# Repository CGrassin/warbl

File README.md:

# WARBL

Fork of the WARBL MIDI wind controller by Andrew Mowry (https://warbl.xyz/).

Adapted layout for 2 layers PCB and USB-C connector - Charles Grassin & [Raphaël Casimir](https://github.com/raphaelcasimir)

## Fabrication notes
You will have to cut the pins of the jack connector so they do not short with the USB-C supports.

## License

WARBL is Open Hardware and is licensed under the CERN OHL version 1.2 and the GNU General Public License.

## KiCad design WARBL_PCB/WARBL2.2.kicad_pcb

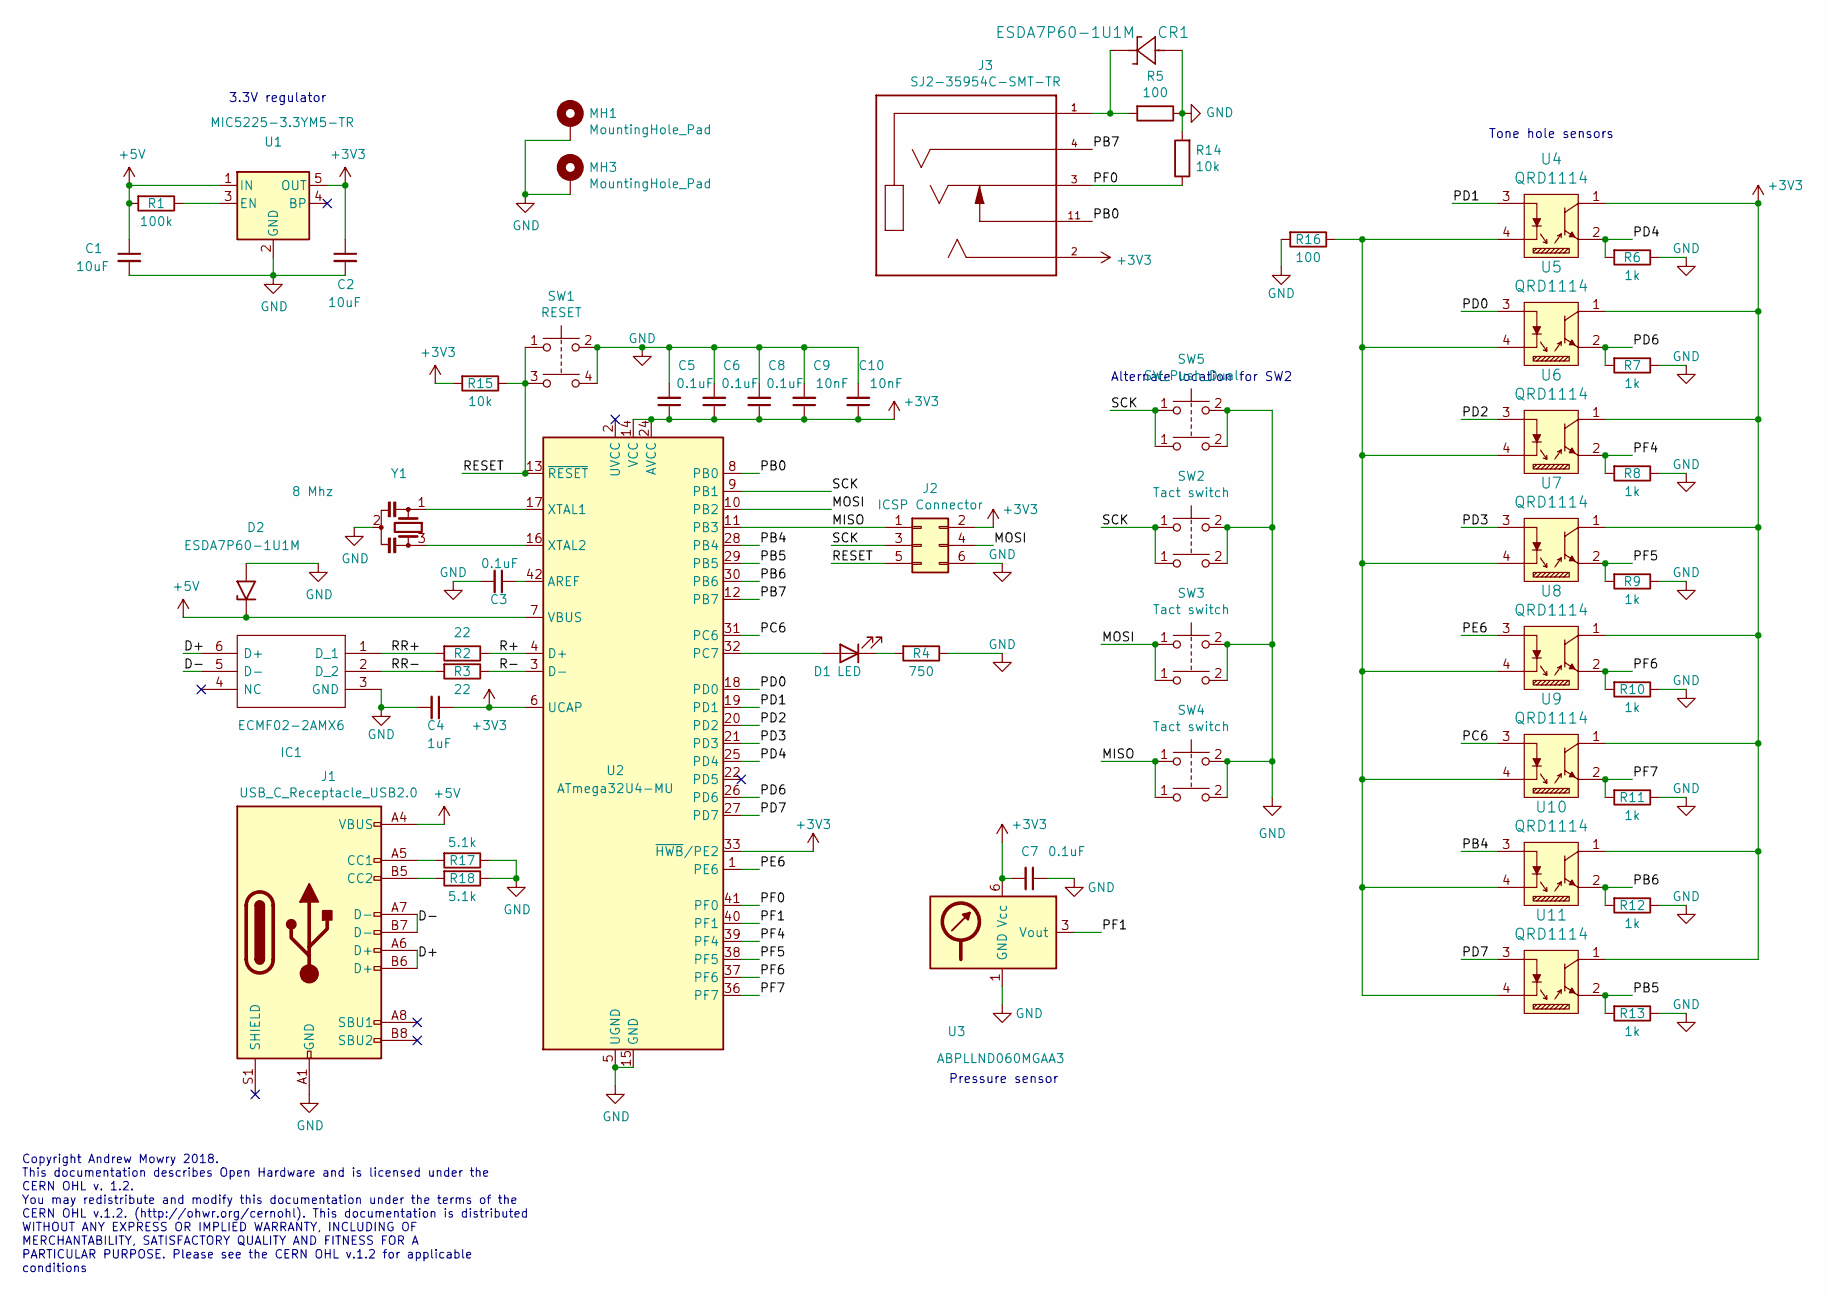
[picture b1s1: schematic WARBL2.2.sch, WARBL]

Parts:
C1, C2: 10uF; C_0603; Mfg Part # CL10A106KQ8NNNC
C3, C5, C6, C7, C8: 0.1uF; C_0603; Mfg Part # CL10F104ZB8NNNC; Digi-Key_PN 0.1µF -20%, +80% 50V Ceramic Capacitor 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
C4: 1uF; C_0603; Mfg Part # CL10B105KP8NNNC
C9, C10: 10nF; C_0603; Mfg Part # CL10B103KB8NCNC; Digi-Key_PN 10000pF ±10% 50V Ceramic Capacitor X7R 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
CR1: ESDA7P60-1U1M
D1: LED; LED_0603; Mfg Part # LG L29K-G2J1-24-Z
D2: ESDA7P60-1U1M; D_DO-201AE_P15.24mm_Horizontal; Mfg Part # ESDA7P60-1U1M
IC1: ECMF02-2AMX6; SON50P150X170X55-6N-D; Mfg Part # ECMF02-2AMX6
J1: USB_C_Receptacle_USB2.0; USB_C_Receptacle_HRO_TYPE-C-31-M-12
J2: ICSP Connector; PinHeader_2x03_P2.54mm_Vertical
J3: SJ2-35954C-SMT-TR; WARBL_CUI_SJ2-35954C-SMT-TR
MH1, MH3: MountingHole_Pad; MountingHole_0.089in_2_56_Pad
R1: 100k; R_0603; Mfg Part # ERJ-3EKF1003V; Digi-Key_PN 100 kOhms ±1% 0.1W, 1/10W Chip Resistor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
R2, R3: 22; R_0603_1608Metric; Mfg Part # ERJ-3EKF22R0V; Digi-Key_PN 22 Ohms ±1% 0.1W, 1/10W Chip Resistor 0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
R4: 750; R_0603; Mfg Part # ERJ-3GEYJ751V; Digi-Key_PN 750 Ohms ±5% 0.1W, 1/10W Chip Resistor 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
R5: 100; R_0603_1608Metric
R6, R7, R8, R9, R10, R11, R12, R13: 1k; R_0603; Mfg Part # ERJ-3GEYJ102V
R14: 10k; R_0603_1608Metric
R15: 10k; R_0603; Mfg Part # ERJ-3GEYJ103V
R16: 100; R_0603; Mfg Part # ERJ-3EKF1000V
R17, R18: 5.1k; R_0603_1608Metric; Mfg Part # ERJ-3GEYJ103V
SW1: RESET; SW_KMR221GLFS; Mfg Part # KMR211GLFS
SW2, SW3, SW4: Tact switch; TL3305BF160QG
SW5: SW_Push_Dual; TL3305BF160QG
U1: 3.3V; SOT-23-5; Mfg Part # MIC5225-3.3YM5-TR
U2: ATmega32U4-MU; QFN-44-1EP_7x7mm_Pitch0.5mm; Mfg Part # ATMEGA32U4-MU
U3: ABPLLND060MGAA3
U4, U5, U6, U7, U8, U9, U10, U11: QRD1114; Reflective_Sensor_QRD1114; MPN QRD1114; Digi-Key_PN QRD1114-ND
Y1: 8 Mhz; CSTNE16M0V530000R0; Mfg Part # CSTNE8M00GH5L000R0

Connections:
+3V3: C2.1, C4.1, C5.1, C6.1, C7.2, C8.1, C9.1, C10.1, J2.2, J3.2, R15.2, U1.5 (OUT), U2.6 (UCAP), U2.14 (VCC), U2.24 (AVCC), U2.33 (~HWB~/PE2), U2.34 (VCC), U2.44 (AVCC), U3.6 (Vcc), U4.1, U5.1, U6.1, U7.1, U8.1, U9.1, U10.1, U11.1
+5V: C1.1, D2.1 (A1), J1.A4 (VBUS), J1.A9 (VBUS), J1.B4 (VBUS), J1.B9 (VBUS), R1.2, U1.1 (IN), U2.7 (VBUS)
/D+: IC1.6 (D+), J1.A6 (D+), J1.B6 (D+)
/D-: IC1.5 (D-), J1.A7 (D-), J1.B7 (D-)
/MISO: J2.1, SW4.1, U2.11 (PB3)
/MOSI: J2.4, SW3.1, U2.10 (PB2)
/PB0: J3.11, U2.8 (PB0)
/PB4: U2.28 (PB4), U10.3
/PB5: R13.2, U2.29 (PB5), U11.2
/PB6: R12.2, U2.30 (PB6), U10.2
/PB7: J3.4, U2.12 (PB7)
/PC6: U2.31 (PC6), U9.3
/PD0: U2.18 (PD0), U5.3
/PD1: U2.19 (PD1), U4.3
/PD2: U2.20 (PD2), U6.3
/PD3: U2.21 (PD3), U7.3
/PD4: R6.2, U2.25 (PD4), U4.2
/PD6: R7.2, U2.26 (PD6), U5.2
/PD7: U2.27 (PD7), U11.3
/PE6: U2.1 (PE6), U8.3
/PF0: J3.3, R14.1, U2.41 (PF0)
/PF1: U2.40 (PF1), U3.3 (Vout)
/PF4: R8.2, U2.39 (PF4), U6.2
/PF5: R9.2, U2.38 (PF5), U7.2
/PF6: R10.2, U2.37 (PF6), U8.2
/PF7: R11.2, U2.36 (PF7), U9.2
/R+: R2.1, U2.4 (D+)
/R-: R3.1, U2.3 (D-)
/RESET: J2.5, R15.1, SW1.1, SW1.3, U2.13 (~RESET)
/RR+: IC1.1 (D_1), R2.2
/RR-: IC1.2 (D_2), R3.2
/SCK: J2.3, SW2.1, SW5.1, U2.9 (PB1)
GND: C1.2, C2.2, C3.2, C4.2, C5.2, C6.2, C7.1, C8.2, C9.2, C10.2, CR1.2, D2.2 (A2), IC1.3 (GND), J1.A1 (GND), J1.A12 (GND), J1.B1 (GND), J1.B12 (GND), J2.6, MH1.1, MH3.1, R4.1, R5.1, R6.1, R7.1, R8.1, R9.1, R10.1, R11.1, R12.1, R13.1, R14.2, R16.2, R17.1, R18.1, SW1.2, SW1.4, SW2.2, SW3.2, SW3.4, SW4.2, SW5.2, U1.2 (GND), U2.5 (UGND), U2.15 (GND), U2.23 (GND), U2.35 (GND), U2.43 (GND), U2.45 (GND), U3.1 (GND), Y1.2
unnamed: C3.1, U2.42 (AREF)
unnamed: CR1.1, J3.1, R5.2
unnamed: D1.1 (K), R4.2
unnamed: D1.2 (A), U2.32 (PC7)
unnamed: J1.A5 (CC1), R17.2
unnamed: J1.B5 (CC2), R18.2
unnamed: R1.1, U1.3 (EN)
unnamed: R16.1, U4.4, U5.4, U6.4, U7.4, U8.4, U9.4, U10.4, U11.4
unnamed: U2.16 (XTAL2), Y1.3
unnamed: U2.17 (XTAL1), Y1.1

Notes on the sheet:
Tone hole sensors
3.3V regulator
Pressure sensor
Copyright Andrew Mowry 2018. This documentation describes Open Hardware and is licensed under the CERN OHL v. 1.2. You may redistribute and modify this documentation under the terms of the CERN OHL v.1.2. (http://ohwr.org/cernohl). This documentation is distributed WITHOUT ANY EXPRESS OR IMPLIED WA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
Alternate location for SW2

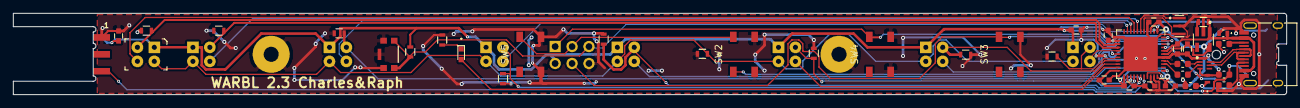
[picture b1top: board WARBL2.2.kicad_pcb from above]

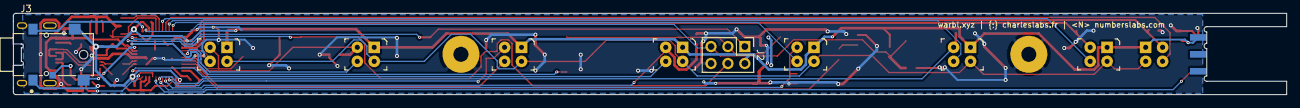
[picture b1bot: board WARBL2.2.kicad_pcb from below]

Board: 4 copper layers, 191.2 x 12.2 mm, 54 parts (9 on the bottom side), 43 nets.

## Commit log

2020-08-20 Added original PCB files
2020-08-20 Prepared PCB for 2 layers routing
2020-08-25 First routing try, USB side of PCB done
2020-08-25 Changed footprints, added again jack connector, no routing
2020-08-25 Routed jack connector and all its components, modified board outlines to accomodate
2020-08-26 Routed front and lower pins of the uC
2020-08-26 Routed everything but ground
2020-08-26 Finished board routing
2020-08-27 Cleaned silkscreen and added Gerbers
2020-08-27 Deleted no-copper zones that were present on original design and re-generated gerbers/zip
2020-08-29 Better ground loops, better thermal relief for USB-C, improved some tracks routing
2020-08-31 Resistor was behind a button
2020-08-31 Added interractive BOM file

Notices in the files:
parts and their libraries:
Copyright 2016 Accelerated Designs. All rights reserved.
